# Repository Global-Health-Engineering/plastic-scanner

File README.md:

## Plastic Scanner
The goal of this project is to build a minimum viable product of the open-source [PlasticScanner](https://github.com/Plastic-Scanner) project and assess its suitability for the Global Health Engineering Lab. The design builds on the existing expertise of the project and incorporates the newest hardware version, Development Board 2.3. The overall objective of the project is to evaluate the scanner’s adaptability to the use case in Malawi and identify opportunities for improvement. This scanner is fully functional and can be reproduced for testing and development purposes. However, it is not recommended for any commercial application. Further development is still required.

## Introduction
Plastic is a widely used material, inexpensive to manufacture, and therefore a common choice for single-use products. However, due to its extensive use, global plastic pollution and its subsequent degradation in landfills into micro- and nanoplastics are threatening ecosystems (Walker & Fequet, 2023). Estimates indicate that plastic consumption will increase from 464 Mt/y in 2020 to over 700 Mt/y by 2050 (Dokl et al., 2024). Plastic recycling is established, but it first requires thorough separation of plastic components. Industrial plastic scanners employ various spectroscopic methods, with Near-Infrared (NIR) spectroscopy being the primary technology (Werner et al., 2023). Light is emitted, and the reflected relative light intensity from the material is measured to identify its composition.

Especially for small-scale recycling facilities and projects with limited financial resources, commercial plastic scanners are extremly expensive. Sorting is therefore done manually, which is often labor-intensive and inaccurate. An example is WASTE Adviser (WASTE Adviser Website, 2025), an NGO in Malawi that is establishing plastic beneficiation pathways for PET and HDPE. For the quality of the upcycled product, it is essential that the plastic is sorted with high accuracy. Otherwise, the recycled product suffers from embrittlement.

The PlasticScanner is an open source project which developed a low-cost plastic identification method. Utilizing inexpensive infrared LEDs and a machine learning model to identify the following six types of plastic:

## How it works
The PlasticScanner allows the identification of six different plastic types using an approach called discrete near-infrared (NIR) spectroscopy. The IR LEDs on the Scanner module emit light one by one for a short period of time. Each time, the reflectance of the emitted light is measured by a photodiode.

This results in a spectral analysis of the measured reflectance. Plastic identification is performed by comparing each measurement with the distinct reflectance spectra of the six plastic types (see illustration, for visualization only, not to scale). Since the device only provides eight readings at specific wavelengths and the actual reflectance spectra of plastics can be very similar, a machine learning model is applied. The model helps identify plastics more reliably without requiring a full spectral sweep. Additional information, such as color, can further improve the model, as dark plastics are particularly challenging to identify with this method.

## Handheld Device

Components:
- 3D printed enclosure
- Scanning PCB (I²C for data transfer)
- Lilygo T-RGB UI interface, ESP32-S3 Microcontroller, USB-C port, Battery recharging, (I²C for data transfer)
- 3.7V 2600mAh Battery
- Button
- Power on/off shifter

## Future Work
- Create Training Data for machine learning Model with correct  IR LED range
- Retrain machine learning Model
- Add Color Sensor in Firmware
- Testing
- Supplychain addaptations (IR LED sourcing problems)

There is still a lot to improve! The most important point is that the current machine learning model still uses the old dataset, which relied on different IR LED ranges. To finalize this device, the model would need to be retrained with data for the wavelengths actually used (see Firmware). Due to this, testing has not yet been performed. Establishing the accuracy of the device and testing it for the intended use case is of high importance. The color sensor is included on the PCB but has not yet been implemented in the firmware. For future designs, the supplier of the IR LEDs should be changed, as especially high-wavelength LEDs are difficult to source and often have long delivery times. Switching to through-hole LEDs would increase the number of available suppliers and simplify sourcing.

## References
PlasticScanner Website: https://plasticscanner.com/ 

PlasticScanner Github: [Plastic-Scanner Project](https://github.com/Plastic-Scanner)

PCB: Lawrence R Kincheloe III, [handheld scanner](https://github.com/LokiMetaSmith/handheld-scanner.git)

CAD: Markus Glavind, [handheld scanner](https://github.com/Plastic-Scanner/handheld-scanner.git) 

Walker, T. R., & Fequet, L. (2023). Current trends of unsustainable plastic production and micro(nano)plastic pollution. TrAC Trends in Analytical Chemistry, 160, 116984. https://doi.org/10.1016/j.trac.2023.116984

Dokl, M., Copot, A., Krajnc, D., Fan, Y. V., Vujanović, A., Aviso, K. B., Tan, R. R., Kravanja, Z., & Čuček, L. (2024). Global projections of plastic use, end-of-life fate and potential changes in consumption, reduction, recycling and replacement with bioplastics to 2050. Sustainable Production and Consumption, 51, 498–518. https://doi.org/10.1016/j.spc.2024.09.025 

Werner, T., Taha, I., & Aschenbrenner, D. (2023). An overview of polymer identification techniques in recycling plants with focus on current and future challenges. Procedia CIRP, 120, 1381–1386. https://doi.org/10.1016/j.procir.2023.09.180

WASTE Adviser Website. (2025, Oktober 7). https://www.wasteadvisersmw.org/eu-building-better

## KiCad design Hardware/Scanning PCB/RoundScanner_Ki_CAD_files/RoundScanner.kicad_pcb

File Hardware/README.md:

## Hardware

The hardware has the following components:

- Scanning PCB
- Lilygo T-RGB (ESP32-S3, Touch Screen, Battery recharging cycle, USB-C port, SD card)
- Button
- on/off Switch
- 3.7V 2600mAh Battery, rechargable 

Since the Lilygo board does not provide any dedicated external input pins, the onboard BOOT button was repurposed as an external input. Although the Scanning PCB includes additional external inputs, using them would require transmitting an extra button signal over the existing I²C link between the two boards, which would significantly increase implementation complexity.

## Scanning PCB
The scanning PCB was adapted from Lawrence Kincheloe's design, which represents the latest version of the handheld PlasticScanner. The IR LED wavelengths were modified to use available LEDs, and a few resistor values were adjusted accordingly.

Lawrence R Kincheloe III, [handheld scanner](https://github.com/LokiMetaSmith/handheld-scanner.git)

The PCB was soldered by hand using low-temperature solder paste, a soldering iron, a hot-air gun, and a microscope. The 1650nm IR LED is still missing, since its delivery data has been pushed to the 18.08.2026. 

## Further Work
- IR LED sourcing problems -> change to push through LED's instead of SMD
- Separated LED PCB (first design exists)
- Find better solution for Button Signal (currently BOOT Button repurposed as an external input)
- to reduce cost the design could be changerd to only one photodiode or the LED count could be reduced

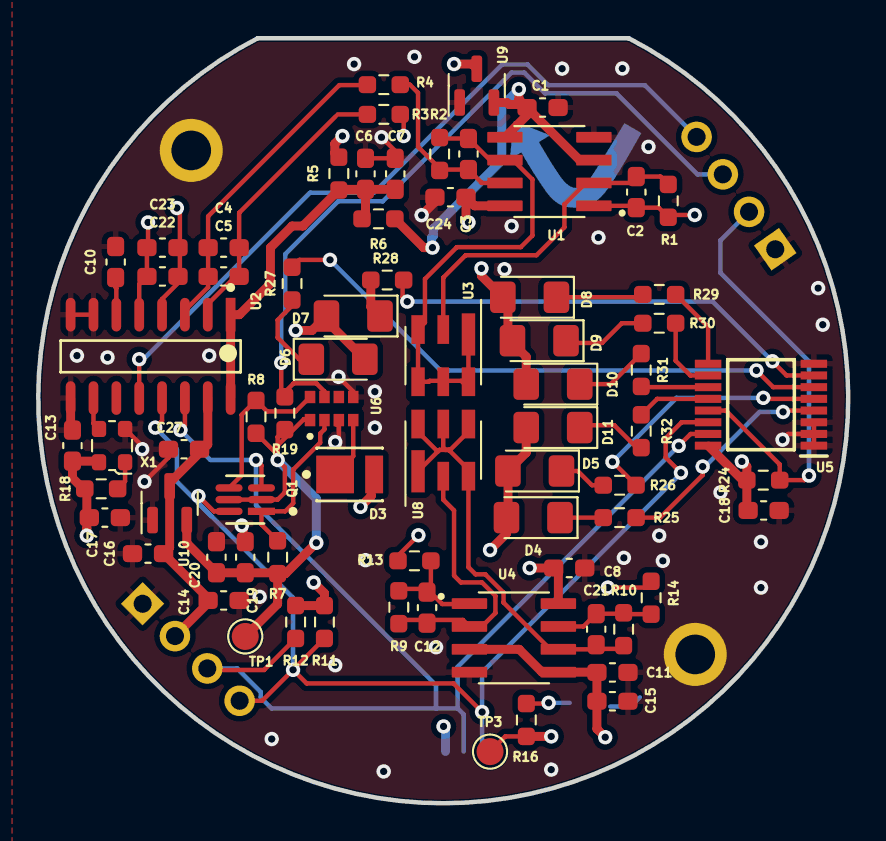
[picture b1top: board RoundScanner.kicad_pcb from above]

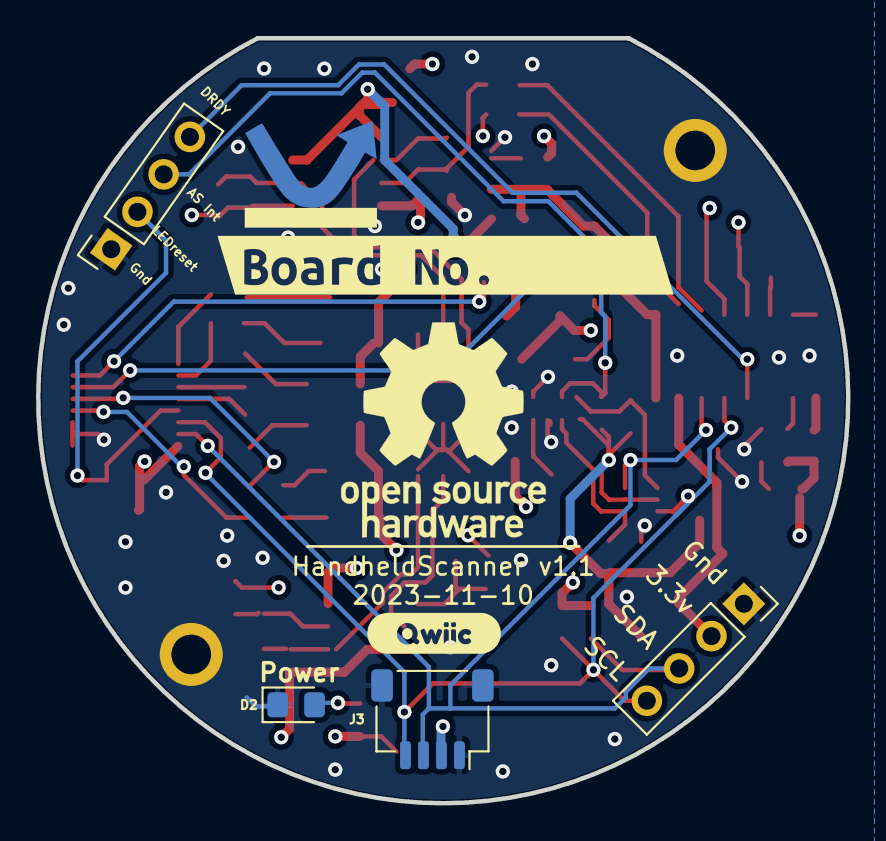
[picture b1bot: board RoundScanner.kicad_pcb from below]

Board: 4 copper layers, 45.0 x 42.5 mm, 79 parts (6 on the bottom side), 45 nets.

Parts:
C1, C7, C10, C11, C13, C16, C18, C20, C27: 0.1uF; C_0603_1608Metric_Pad1.08x0.95mm_HandSolder
C2, C3, C12, C21: 51pF; C_0603_1608Metric_Pad1.08x0.95mm_HandSolder
C4, C22: 47nF; C_0603_1608Metric_Pad1.08x0.95mm_HandSolder
C5, C23: 100pF; C_0603_1608Metric_Pad1.08x0.95mm_HandSolder
C6, C8, C24: 1uF; C_0603_1608Metric_Pad1.08x0.95mm_HandSolder
C14, C15, C19: 10uF; C_0603_1608Metric_Pad1.08x0.95mm_HandSolder
C17: 22uF; C_0603_1608Metric_Pad1.08x0.95mm_HandSolder
D2: POWER LED; LED_0805_2012Metric_Pad1.15x1.40mm_HandSolder
D3: EAHC2835WD6; Everlight-EAHC2835WD6-MFG
D4: 855nm; LED_1206_3216Metric_Pad1.42x1.75mm_HandSolder
D5: 940nm; LED_1206_3216Metric_Pad1.42x1.75mm_HandSolder
D6: 1050nm; LED_1206_3216Metric_Pad1.42x1.75mm_HandSolder
D7: 1300nm; LED_1206_3216Metric_Pad1.42x1.75mm_HandSolder
D8: 1460nm; LED_1206_3216Metric_Pad1.42x1.75mm_HandSolder
D9: 1550nm; LED_1206_3216Metric_Pad1.42x1.75mm_HandSolder
D10: 1650nm; LED_1206_3216Metric_Pad1.42x1.75mm_HandSolder
D11: 1720nm; LED_1206_3216Metric_Pad1.42x1.75mm_HandSolder
J2: Conn_01x09; round_notch
J3: SM04B-SRSS-TB; JST_SH_SM04B-SRSS-TB_1x04-1MP_P1.00mm_Horizontal
LOGO1: OSHW-Logo_11.4x12mm_SilkScreen
LOGO2: PlasticScannerLogo
Q1: BSS138DW-7-F; Diodes_Inc._-_BSS138DW-7-F-A
R1, R2, R9, R10: 240k; R_0603_1608Metric_Pad0.98x0.95mm_HandSolder
R3, R4, R13, R14: 301; R_0603_1608Metric_Pad0.98x0.95mm_HandSolder
R5: NP; R_0603_1608Metric_Pad0.98x0.95mm_HandSolder
R6: 1; R_0603_1608Metric_Pad0.98x0.95mm_HandSolder
R7, R8, R11, R12, R19: 10k; R_0603_1608Metric_Pad0.98x0.95mm_HandSolder
R16, R18, R24: 1k; R_0603_1608Metric_Pad0.98x0.95mm_HandSolder
R25, R26, R27, R28, R29, R30, R31, R32: 43; R_0603_1608Metric_Pad0.98x0.95mm_HandSolder
TP1: Test_1.8V; TestPoint_Pad_D1.5mm
TP3: Test_3.3V; TestPoint_Pad_D1.5mm
U1, U4: OPA2376xxD; SOIC127P599X175-8N
U2: NAU7802SGI; Nuvoton-NAU7802SGI
U3: MTSM2601SMF1-100
U5: TLC59208FIPWR; SOP65P640X120-16N
U6: AS7341-DLGT; PSON80P310X200X110-8N
U8: MTSM1346SMF1-100
U9: AP2127N-2.5; SOT-23
U10: AP2127N-1.8; SOT-23
X1: 4.9152 MHz; Oscillator_SMD_ECS_2520MV-xxx-xx-4Pin_2.5x2.0mm
kibuzzard-6398DD41: G***; kibuzzard-6398DD41
kibuzzard-6346913B: G***; kibuzzard-6346913B

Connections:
+1V8: C19.2, C20.2, Q1.2 (G2), Q1.5 (G1), R7.1, R8.1, R19.1, TP1.1, U6.1 (VDD), U10.2 (VO)
+3.3V: C8.2, C13.1, C14.2, C16.2, C17.1, C18.1, C24.2, C27.2, D3.2 (ANODE), D4.2 (A), D5.2 (A), D6.2 (A), D7.2 (A), D8.2 (A), D9.2 (A), D10.2 (A), D11.2 (A), J2.2, J3.2, R5.2, R11.1, R12.2, R16.1, R18.2, R24.2, TP3.1, U1.8 (V+), U2.15 (DVDD), U4.8 (V+), U5.16 (VCC), U9.3 (VI), U10.3 (VI), X1.4 (VDD)
/ADC/AIN2+: C22.1, C23.2, R14.2, U2.5 (VIN2P)
/ADC/AIN2-: C22.2, C23.1, R13.2, U2.4 (VIN2N)
/ADC/AIN+: C4.1, C5.2, R4.2, U2.3 (VIN1P)
/ADC/AIN-: C4.2, C5.1, R3.2, U2.2 (VIN1N)
/ADC/DRDY_INT: J2.8, U2.12 (DRDY)
/InGaS Sensor/Anode: C2.1, R1.1, U1.2 (-), U3.2 (Anode)
/InGaS Sensor/Anode_2: C12.1, R9.1, U4.2 (-), U8.2 (Anode)
/InGaS Sensor/Cathode: C3.1, R2.2, U1.6 (-), U3.1 (Cathode), U3.3 (Cathode), U3.4 (Cathode), U3.5 (NC), U3.6 (Cathode)
/InGaS Sensor/Cathode_2: C21.1, R10.2, U4.6 (-), U8.1 (Case), U8.3 (Case), U8.4 (Case), U8.5 (Cathode), U8.6 (Case)
/LED/LED_RESET: J2.6, R24.1, U5.13 (~RESET)
/MCU + IO/AS7341_INT: J2.7, R19.2, U6.7 (INT)
/MCU + IO/SCL_2v: Q1.1 (S2), R7.2, U6.2 (SCL)
/MCU + IO/SDA_2v: Q1.4 (S1), R8.2, U6.8 (SDA)
GND: C1.1, C6.1, C7.1, C8.1, C10.1, C11.1, C13.2, C14.1, C15.1, C16.1, C17.2, C18.2, C19.1, C20.1, C24.1, C27.1, D2.1 (K), J2.1, J2.5, J2.MP, J3.1, J3.MP (Pin_5), U1.4 (V-), U2.7 (REFN), U2.8 (AVSS), U2.9 (DVSS), U4.4 (V-), U5.1 (A0), U5.2 (A1), U5.3 (A2), U5.8 (GND), U6.3 (GND), U6.5 (PGND), U9.1 (GND), U10.1 (GND), X1.2 (GND)
unnamed: C2.2, R1.2, R3.1, U1.1
unnamed: C3.2, R2.1, R4.1, U1.7
unnamed: C12.2, R9.2, R13.1, U4.1
unnamed: C21.2, R10.1, R14.1, U4.7
unnamed: D2.2 (A), R16.2
unnamed: D3.1 (CATHODE), U6.4 (LDR)
unnamed: D4.1 (K), R25.2
unnamed: D5.1 (K), R26.2
unnamed: D6.1 (K), R27.2
unnamed: D7.1 (K), R28.2
unnamed: D8.1 (K), R29.2
unnamed: D9.1 (K), R30.2
unnamed: D10.1 (K), R31.2
unnamed: D11.1 (K), R32.2
unnamed: C6.2, C7.2, R5.1, R6.1, U2.1 (REFP), U2.16 (AVDD/LDO)
unnamed: C10.2, U2.6 (VBG)
unnamed: U2.10 (XIN), X1.3 (OUT)
unnamed: R25.1, U5.4 (~OUT0)
unnamed: R26.1, U5.5 (~OUT1)
unnamed: R27.1, U5.6 (~OUT2)
unnamed: R28.1, U5.7 (~OUT3)
unnamed: R29.1, U5.9 (~OUT4)
unnamed: R30.1, U5.10 (~OUT5)
unnamed: R31.1, U5.11 (~OUT6)
unnamed: R32.1, U5.12 (~OUT7)
unnamed: R18.1, X1.1 (Tri-State)
SCL: J2.4, J3.4, Q1.6 (D2), R11.2, U2.13 (SCLK), U5.14 (SCL)
SDA: J2.3, J3.3, Q1.3 (D1), R12.1, U2.14 (SDIO), U5.15 (SDA)
VDDA: C1.2, C11.2, C15.2, R6.2, U1.3 (+), U1.5 (+), U4.3 (+), U4.5 (+), U9.2 (VO)

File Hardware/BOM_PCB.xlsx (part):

Part Number | sourced | placed | Designator | cathode/anode marking | Notes/Name | Footprint | Quantity | Manufacturer | Manufacturer Part Number (MPN) | Vendor / Supplier | Vendor P/N | Stock | Available | Unit Cost (USD) | Cost per device
1 | y | y | PCB Assembly |  | scanner board loki |  | 1 | JLCPCB |  |  |  | 5 | 4 | 1.3599999999999999 | 1.3599999999999999
2 | y | y | C1, C7, C10, C11, C13, C16, C20, C27 |  | 0.1uF 25V | C_0603_1608Metric_Pad1.08x0.95mm_HandSolder | 8 | KEMET | C0603C104K3RACTU | Digikey | 399-C0603C104K3RACTUDKR-ND | 16 | 8 | 0.08 | 0.64
3 | y | y | C2, C3, C12, C21 |  | 51pF 50V | C_0603_1608Metric_Pad1.08x0.95mm_HandSolder | 4 | KEMET | C0603X510K3HACTU | Digikey | 399-C0603X510K3HACTUDKR-ND | 8 | 4 | 0.1 | 0.4
4 | y | y | C14, C15, C19 |  | 10uF 10V | C_0603_1608Metric_Pad1.08x0.95mm_HandSolder | 3 | Murata Electronics | GRM188Z71A106KA73D | Digikey | 490-GRM188Z71A106KA73DDKR-ND | 6 | 3 | 0.28000000000000003 | 0.84000000000000008
5 | y | y | C4, C22 |  | 47nF 50V | C_0603_1608Metric_Pad1.08x0.95mm_HandSolder | 2 | KEMET | C0603X473J4RECAUTO | Digikey | 399-C0603X473J4RECAUTODKR-ND | 4 | 2 | 0.21 | 0.42
6 | y | y | C5, C23 |  | 100pF 50V | C_0603_1608Metric_Pad1.08x0.95mm_HandSolder | 2 | KEMET | C0603C101M3RACAUTO | Digikey | 399-C0603C101M3RACAUTODKR-ND | 4 | 2 | 0.24 | 0.48
7 | y | y | C6, C8, C24 |  | 1uF 25V | C_0603_1608Metric_Pad1.08x0.95mm_HandSolder | 1 | Taiyo Yuden | TMK107B7105KA-T | Digikey | 587-2984-6-ND | 4 | 3 | 0.08 | 0.08
8 | y | y | C17 |  | 22uF 25V | C_0603_1608Metric_Pad1.08x0.95mm_HandSolder | 1 | Murata Electronics | GRM188C61E226ME01W | Digikey | 490-GRM188C61E226ME01WDKR-ND | 4 | 3 | 0.41 | 0.41
9 | y | y | R7, R8, R11, R12, R19 |  | 10k | R_0603_1608Metric_Pad0.98x0.95mm_HandSolder | 5 | Vishay | MCT06030C1002FP500 | Digikey | MCT0603-10.0K-CFDKR-ND | 10 | 5 | 0.1 | 0.5
10 | y | y | R1, R2, R9, R10 |  | 240k | R_0603_1608Metric_Pad0.98x0.95mm_HandSolder | 4 | YAGEO | RT0603FRE07240KL | Digikey | 13-RT0603FRE07240KLDKR-ND | 8 | 4 | 0.1 | 0.4
11 | y | y | R3, R4, R13, R14 |  | 301 | R_0603_1608Metric_Pad0.98x0.95mm_HandSolder | 4 | YAGEO | RT0603FRE07301RL | Digikey | 13-RT0603FRE07301RLDKR-ND | 8 | 4 | 0.1 | 0.4
12 | y | y | R16, R26, R29, R30 |  | 150 | R_0603_1608Metric_Pad0.98x0.95mm_HandSolder | 4 | Vishay | MCT06030C1500FP500 | Digikey | MCT0603-150-CFDKR-ND | 8 | 4 | 0.1 | 0.4
13 | y | y | R18, R16 |  | 1k, R16 = 100 Ohm | R_0603_1608Metric_Pad0.98x0.95mm_HandSolder | 2 | Vishay | MCT06030C1001FP500 | Digikey | MCT0603-1.00K-CFDKR-ND | 4 | 2 | 0.1 | 0.2
14 | y | y | R27, R28 |  | 240 | R_0603_1608Metric_Pad0.98x0.95mm_HandSolder | 2 | Vishay | MCT06030C2400FP500 | Digikey | 749-1760-6-ND | 4 | 2 | 0.1 | 0.2
15 | y | y | R25 |  | 56 | R_0603_1608Metric_Pad0.98x0.95mm_HandSolder | 1 | YAGEO | RT0603FRE0756RL | Digikey | 13-RT0603FRE0756RLDKR-ND | 4 | 3 | 0.1 | 0.1
16 | y | y | R31 |  | 40 | R_0603_1608Metric_Pad0.98x0.95mm_HandSolder | 1 | Stackpole Electronics Inc | RMCF0603FT40R2 | Digikey | RMCF0603FT40R2DKR-ND | 4 | 3 | 0.1 | 0.1
17 | y | y | R32 |  | 130 | R_0603_1608Metric_Pad0.98x0.95mm_HandSolder | 1 | YAGEO | RT0603FRE07130RL | Digikey | 13-RT0603FRE07130RLDKR-ND | 4 | 3 | 0.1 | 0.1
18 | y | y | D2 |  | POWER LED RED | LED_0805_2012Metric_Pad1.15x1.40mm_HandSolder | 1 | Visual Communications Company - VCC | LSM0805412V | Digikey | 28-LSM0805412VDKR-ND | 3 | 2 | 0.43 | 0.43
19 | y | y | D3 | T | EAHC2835WD6 | Everlight-EAHC2835WD6-MFG | 1 | Everlight Electronics Co Ltd | EAHC2835WD6 | Digikey | 1080-1461-6-ND | 2 | 1 | 0.28999999999999998 | 0.28999999999999998
20 | y | y | D4 | T | 850bm DOM | LED_1206_3216Metric_Pad1.42x1.75mm_HandSolder | 1 | Würth Elektronik | 15412085A3060 | Digikey | 732-12009-6-ND | 2 | 1 | 0.56999999999999995 | 0.56999999999999995
21 | y | y | D5 | cathode dot | 940nm DOM | LED_1206_3216Metric_Pad1.42x1.75mm_HandSolder | 1 | SunLED | XZTNI55W-3 | Digikey | 1497-1368-6-ND | 2 | 1 | 0.48 | 0.48
22 | y | y | D6 | cathode dot | 1050nm DOM | LED_1206_3216Metric_Pad1.42x1.75mm_HandSolder | 1 | Marktech Optoelectronics | MTSM5010-843-IR | Digikey | 1125-1359-ND | 2 | 1 | 12.49 | 12.49
23 | y | y | D7 | anode dot | 1200nm DOM | LED_1206_3216Metric_Pad1.42x1.75mm_HandSolder | 1 | Marktech Optoelectronics | MTSM0012-844-IR | Digikey | 1125-MTSM0012-844-IRDKR-ND | 2 | 1 | 13.1 | 13.1
24 | y | y | D8 | anode dot | 1300nm DOM | LED_1206_3216Metric_Pad1.42x1.75mm_HandSolder | 1 | Marktech Optoelectronics | MTSM0013-844-IR | Digikey | 1125-MTSM0013-844-IRDKR-ND | 2 | 1 | 13.1 | 13.1
25 | y | y | D9 | anode dot | 1460nm DOM | LED_1206_3216Metric_Pad1.42x1.75mm_HandSolder | 1 | Marktech Optoelectronics | MTSM6014-844-IR | Digikey | 1125-MTSM6014-844-IRDKR-ND | 2 | 1 | 13.1 | 13.1
26 | y | y | D10 | anode dot | 1550nm DOM not available | LED_1206_3216Metric_Pad1.42x1.75mm_HandSolder | 1 | Marktech Optoelectronics | MTSM5015-194-IR | Digikey | 1125-MTSM5015-194-IRDKR-ND | 2 | 1 | 13.1 | 13.1
27 | y | y | D11 | cathode dot | 1650nm DOM not available | LED_1206_3216Metric_Pad1.42x1.75mm_HandSolder | 1 | Marktech Optoelectronics | MTSM5016-843-IR or MTSM5016-199-IR | Digikey | 1125-1362-ND | 0 | -1 | 23.9 | 23.9
28 | y | y | U1, U4 |  | OPA2376AID | SOIC127P599X175-8N | 2 | Texas Instruments | OPA2376AID | Digikey | 296-26263-5-ND | 3 | 1 | 3.15 | 6.3
29 | y | y | U2 |  | NAU7802SGI | Nuvoton-NAU7802SGI | 1 | Nuvoto Technology Corporation | NAU7802SGI | Digikey | NAU7802SGI-ND | 3 | 2 | 1.62 | 1.62
30 | y | y | U3 |  | MTSM2601SMF1-100 | SENSOR PHOTODIODE 800-2600NM SMD | 1 | Marktech Optoelectronics | MTSM2601SMF1-100 | Digikey | 1125-MTSM2601SMF1-100-ND | 1 | 0 | 36.619999999999997 | 36.619999999999997
31 | y | y | U5 |  | TLC59208FIPWR | SOP65P640X120-16N | 1 | Texas Instruments | TLC59208FIPWR | Digikey | 296-36508-6-ND | 3 | 2 | 1.97 | 1.97
32 | y | y | U6 |  | AS7341-DLGT | PSON80P310X200X110-8N | 1 | ams-OSRAM USA INC. | AS7341-DLGT | Digikey | AS7341-DLGTDKR-ND | 2 | 1 | 7.64 | 7.64
33 | y | y | U7 |  | AP7312-1833W6-7 | AP7312-1833W6-7 | 1 | Diodes Incorporated | AP7312-1833W6-7 | Digikey | AP7312-1833W6-7DIDKR-ND | 2 | 1 | 0.53 | 0.53
34 | y | y | U8 |  | MTSM1346SMF1-100 | SENSOR PHOTODIODE 1300NM 6SMD | 1 | Marktech Optoelectronics | MTSM1346SMF1-100 | Digikey | 1125-MTSM1346SMF1-100-ND | 1 | 0 | 33.549999999999997 | 33.549999999999997
35 | y | y | U9 |  | AP2120N-2.5TRG1 | IC REG LINEAR 2.5V 150MA SOT23 | 1 | Diodes Incorporated | AP2120N-2.5TRG1 | Digikey | AP2120N-2.5TRG1DICT-ND | 3 | 2 | 0.14000000000000001 | 0.14000000000000001
36 | y | y | U10 |  | AP2125N-1.8TRG1 | IC REG LINEAR 1.8V 300MA SOT23-3 | 1 | Diodes Incorporated | AP2125N-1.8TRG1 | Digikey | AP2125N-1.8TRG1DICT-ND | 3 | 2 | 0.17 | 0.17
37 | y | y | X1 |  | 4.9152 MHz | Oscillator_SMD_ECS_2520MV-xxx-xx-4Pin_2.5x2.0mm | 1 | ECS Inc. | ECS-2520MVLC-049-BN-TR | Digikey | 50-ECS-2520MVLC-049-BN-DKR-ND | 3 | 2 | 1.24 | 1.24
38 | y | y | Q1 |  | BSS138DW-7-F | Diodes_Inc._-_BSS138DW-7-F-A | 1 | Diodes Incorporated | BSS138DW-7-F | Digikey | BSS138DW-FDIDKR-ND | 2 | 1 | 0.45 | 0.45
39 | y | y | J1 |  | ThroughHole Pin socket | PinSocket_1x04_P2.54mm_Vertical | 1 |  |  |  |  | 5 | 4 | 0 | 0
40 | y | y | J3 |  | I2C JST socket | JST_SH_SM04B-SRSS-TB_1x04-1MP_P1.00mm_Horizontal | 1 | JST Sales America Inc. | SM04B-SRSS-TB | Digikey | 455-SM04B-SRSS-TBDKR-ND | 5 | 4 | 0.5 | 0.5
41 | y | y | J4 |  | ThroughHole Pin socket | PinSocket_1x04_P2.54mm_Vertical | 1 |  |  |  |  | 5 | 4 | 0 | 0
42 | y | y |  | Assembly component | Button |  | 1 | Lumex Opto/Components Inc. | WS48M-A12RGB12 | Digikey | 67-WS48M-A12RGB12-ND | 1 | 1 | 18.3 | 18.3
43 | y | y |  | Assembly component | On/off switch |  | 1 | C&K | OS102011MS2QN1 | Digikey | CKN9565-ND | 1 | 1 | 0.71 | 0.71
44 | y | y |  | Assembly component | LilyGo-TRGB |  | 1 | LilyGo | Lilygo T-RGB ESP32-S3 2.1/2.8 round display | Lilygo |  | 1 | 1 | 30.04 | 30.04
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
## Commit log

2026-01-15 initialize Readme
2026-01-15 License add
2026-01-16 readme update
2026-01-18 hardware cleaned folders initial upload
2026-01-18 BOM.csv
2026-01-21 Firmware add
2026-01-21 readme update firmware
2026-01-21 structure update
2026-01-22 BOM as xlsx
2026-01-22 image update
2026-01-22 readme updates
2026-01-22 added firmware references
2026-01-22 added references
2026-01-22 change image size
2026-01-22 step files add
2026-01-22 reference add
2026-01-22 image size
